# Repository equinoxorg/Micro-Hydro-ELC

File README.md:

hydrocontroller-hardware-designs
================================

This repository holds PCB/hardware designs for the e.quinox Kingfisher Micro Hydro Power Plant Controller.

Edit

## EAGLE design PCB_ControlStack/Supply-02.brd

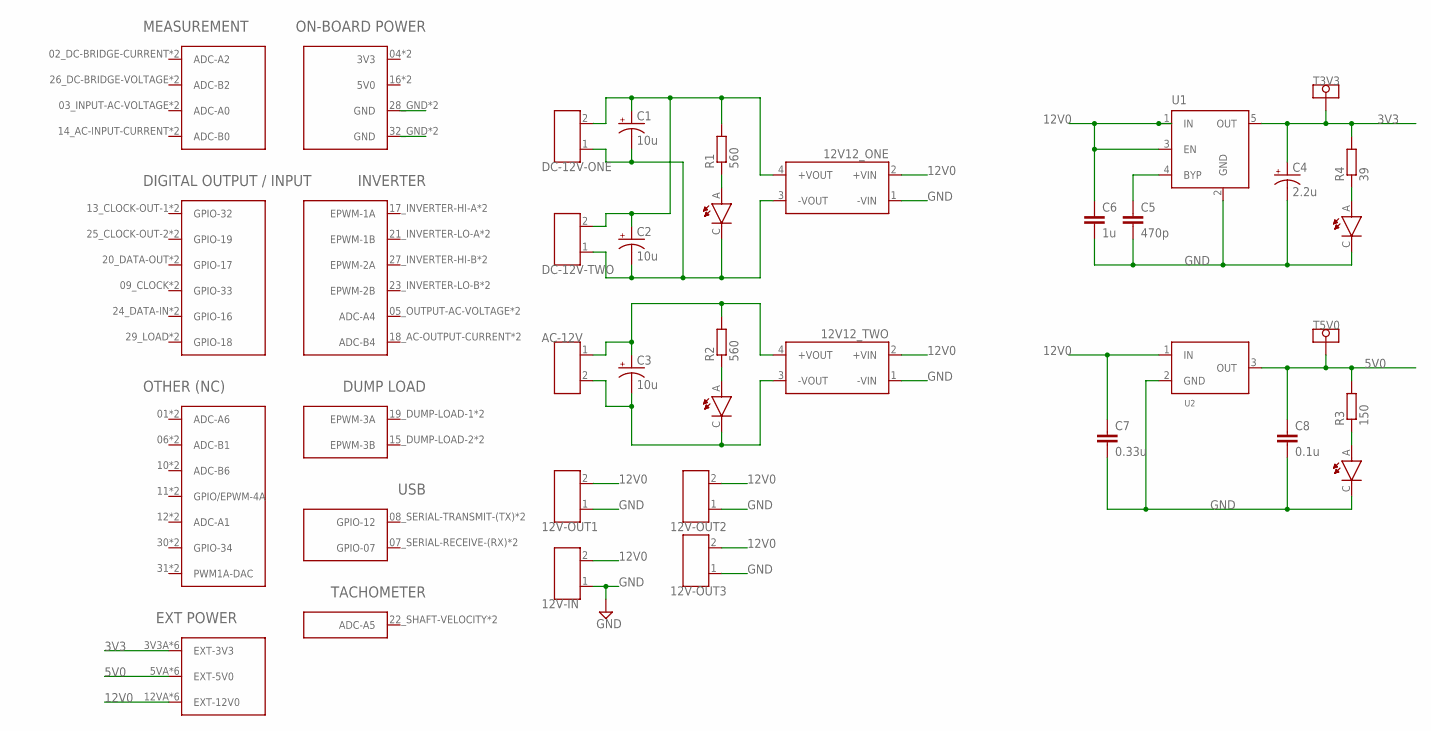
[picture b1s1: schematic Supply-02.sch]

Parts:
12V12_ONE, 12V12_TWO: 12V12_ISO_REG; SIL_REG
12V-IN, 12V-OUT1, 12V-OUT2, 12V-OUT3: 1X2_7,5_TB
AC-12V: 1X2_7,5_TB
C1, C2, C3: 10u; CPOL-4.0MM
C4: 2.2u; CPOL-4.0MM
C5: 470p; C0805
C6: 1u; C0805
C7: 0.33u; C0805
C8: 0.1u; C0805
DC-12V-ONE, DC-12V-TWO: 1X2_7,5_TB
H1: CONTROLLER_STACK
LED1, LED2, LED3, LED4: PLCC2
R1, R2: 560; R0805
R3: 150; R0805
R4: 39; R0805
T3V3, T5V0: TESTPAD
U1: MIC5219XX; SOT23-5
U2: 10V5V-REG-H; TO-220H

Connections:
3V3: C4.+, H1.3V3A (EXT-3V3), H1.3V3B (EXT-3V3), H1.3V3C (EXT-3V3), H1.3V3D (EXT-3V3), H1.3V3E (EXT-3V3), H1.3V3F (EXT-3V3), R4.2, T3V3.TP, U1.5 (OUT)
5V0: C8.1, H1.5VA (EXT-5V0), H1.5VB (EXT-5V0), H1.5VC (EXT-5V0), H1.5VD (EXT-5V0), H1.5VE (EXT-5V0), H1.5VF (EXT-5V0), R3.2, T5V0.TP, U2.3 (OUT)
12V0: 12V12_ONE.2 (+VIN), 12V12_TWO.2 (+VIN), 12V-IN.2, 12V-OUT1.2, 12V-OUT2.2, 12V-OUT3.2, C6.1, C7.1, H1.12VA (EXT-12V0), H1.12VB (EXT-12V0), H1.12VC (EXT-12V0), H1.12VD (EXT-12V0), H1.12VE (EXT-12V0), H1.12VF (EXT-12V0), U1.1 (IN), U1.3 (EN), U2.1 (IN)
GND: 12V12_ONE.1 (-VIN), 12V12_TWO.1 (-VIN), 12V-IN.1, 12V-OUT1.1, 12V-OUT2.1, 12V-OUT3.1, C4.-, C5.2, C6.2, C7.2, C8.2, H1.28_GND (GND), H1.32_GND (GND), H1.C28 (GND), H1.C32 (GND), LED3.C, LED4.C, U1.2 (GND), U2.2 (GND)
unnamed: 12V12_ONE.4 (+VOUT), C1.+, C2.+, DC-12V-ONE.2, DC-12V-TWO.2, R1.2
unnamed: 12V12_ONE.3 (-VOUT), C1.-, C2.-, DC-12V-ONE.1, DC-12V-TWO.1, LED1.C
unnamed: LED1.A, R1.1
unnamed: LED3.A, R3.1
unnamed: 12V12_TWO.3 (-VOUT), AC-12V.2, C3.-, LED2.C
unnamed: C5.1, U1.4 (BYP)
unnamed: LED2.A, R2.1
unnamed: 12V12_TWO.4 (+VOUT), AC-12V.1, C3.+, R2.2
unnamed: LED4.A, R4.1

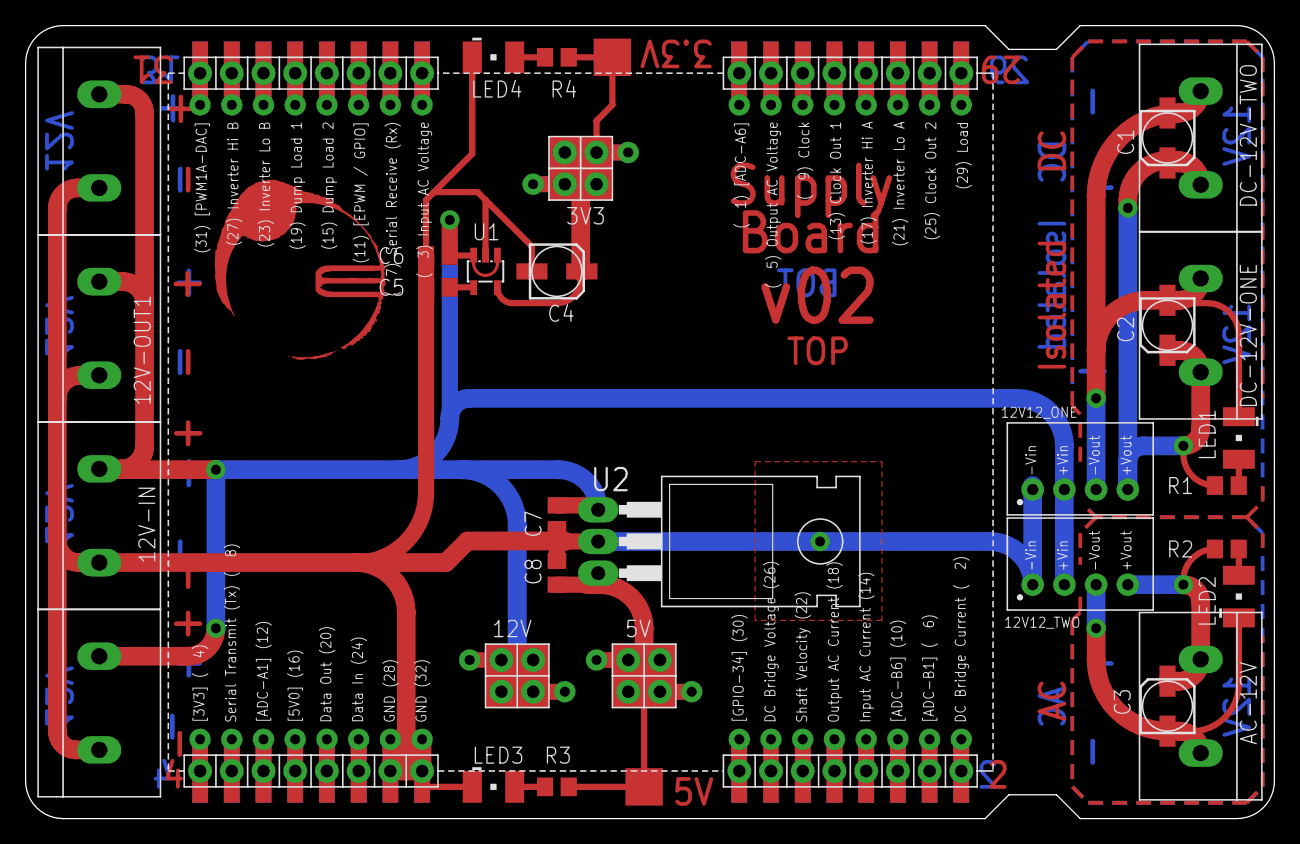
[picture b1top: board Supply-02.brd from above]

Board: 2 copper layers, 100.0 x 63.5 mm, 30 parts (0 on the bottom side), 13 nets.

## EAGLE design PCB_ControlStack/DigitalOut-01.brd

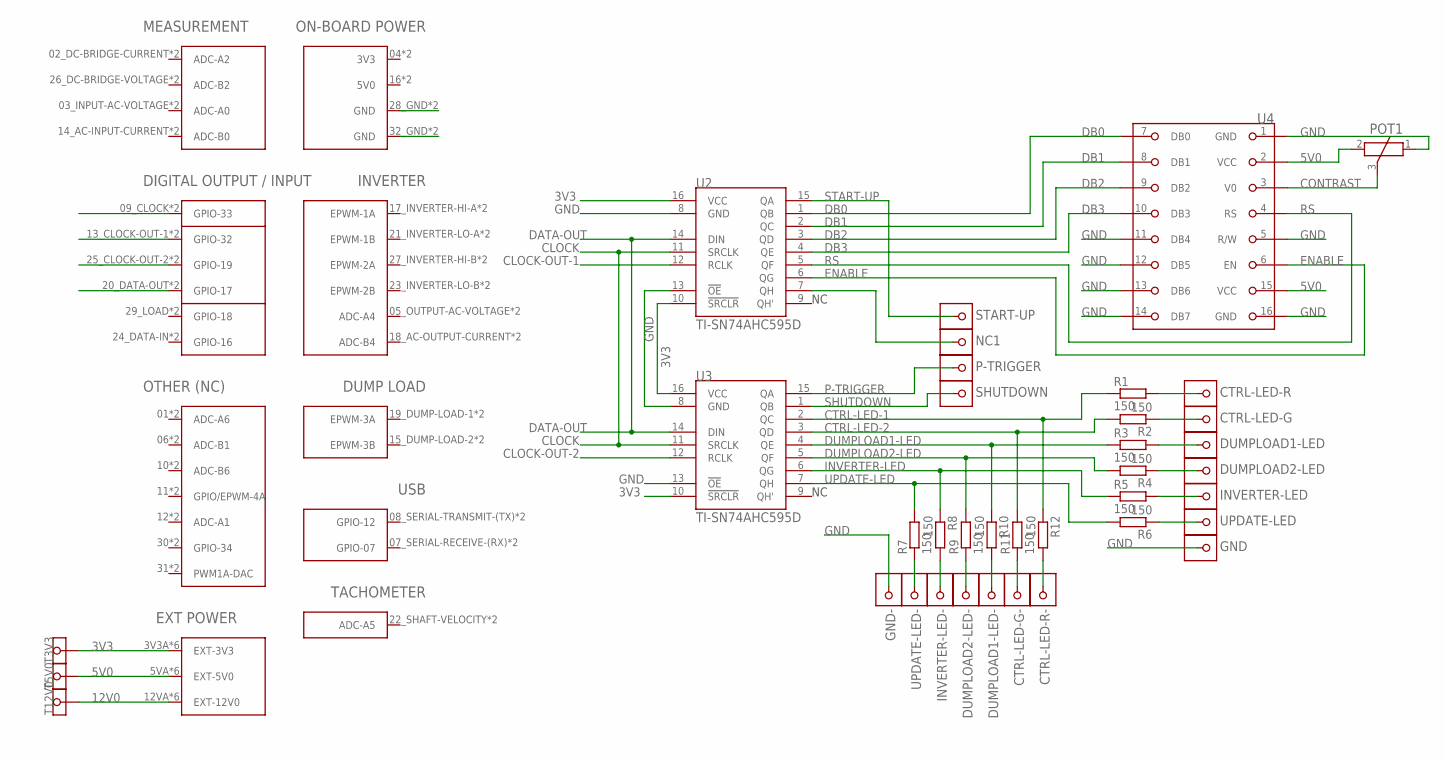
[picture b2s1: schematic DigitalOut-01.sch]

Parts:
CTRL-LED-G: 1X1HEADER(W/VIA)
CTRL-LED-G-: 1X1HEADER
CTRL-LED-R: 1X1HEADER(W/VIA)
CTRL-LED-R-: 1X1HEADER
DUMPLOAD1-LED, DUMPLOAD2-LED: 1X1HEADER(W/VIA)
DUMPLOAD1-LED-, DUMPLOAD2-LED-: 1X1HEADER
GND: 1X1HEADER(W/VIA)
GND-: 1X1HEADER
INVERTER-LED: 1X1HEADER(W/VIA)
INVERTER-LED-: 1X1HEADER
NC1: 1X1HEADER(W/VIA)
P-TRIGGER: 1X1HEADER(W/VIA)
POT1: BOURNS-3361S
R1, R2, R3, R4, R5, R6, R7, R8, R9, R10, R11, R12: 150; R0805
SHUTDOWN: 1X1HEADER(W/VIA)
START-UP: 1X1HEADER(W/VIA)
T3V3, T5V0, T12V0: TESTPAD
U1: CONTROLLER_STACK
U2, U3: TI-SN74AHC595D; SOIC-16D
U4: MULTICOMP-MC9B232
UPDATE-LED: 1X1HEADER(W/VIA)
UPDATE-LED-: 1X1HEADER

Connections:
3V3: T3V3.TP, U1.3V3A (EXT-3V3), U1.3V3B (EXT-3V3), U1.3V3C (EXT-3V3), U1.3V3D (EXT-3V3), U1.3V3E (EXT-3V3), U1.3V3F (EXT-3V3), U2.10 (!SRCLR), U2.16 (VCC), U3.10 (!SRCLR), U3.16 (VCC)
5V0: POT1.2, T5V0.TP, U1.5VA (EXT-5V0), U1.5VB (EXT-5V0), U1.5VC (EXT-5V0), U1.5VD (EXT-5V0), U1.5VE (EXT-5V0), U1.5VF (EXT-5V0), U4.2 (VCC), U4.15 (VCC)
12V0: T12V0.TP, U1.12VA (EXT-12V0), U1.12VB (EXT-12V0), U1.12VC (EXT-12V0), U1.12VD (EXT-12V0), U1.12VE (EXT-12V0), U1.12VF (EXT-12V0)
CLOCK: U1.09_CLOCK (GPIO-33), U1.C9 (GPIO-33), U2.11 (SRCLK), U3.11 (SRCLK)
CLOCK-OUT-1: U1.13_CLOCK-OUT-1 (GPIO-32), U1.C13 (GPIO-32), U2.12 (RCLK)
CLOCK-OUT-2: U1.25_CLOCK-OUT-2 (GPIO-19), U1.C25 (GPIO-19), U3.12 (RCLK)
CONTRAST: POT1.3, U4.3 (V0)
CTRL-LED-1: R1.1, R12.1, U3.2 (QC)
CTRL-LED-2: R2.2, R11.2, U3.3 (QD)
DATA-OUT: U1.20_DATA-OUT (GPIO-17), U1.C20 (GPIO-17), U2.14 (DIN), U3.14 (DIN)
DB0: U2.1 (QB), U4.7 (DB0)
DB1: U2.2 (QC), U4.8 (DB1)
DB2: U2.3 (QD), U4.9 (DB2)
DB3: U2.4 (QE), U4.10 (DB3)
DUMPLOAD1-LED: R3.1, R10.1, U3.4 (QE)
DUMPLOAD2-LED: R4.2, R9.2, U3.5 (QF)
ENABLE: U2.6 (QG), U4.6 (EN)
GND: GND.P$2, GND.P$3, GND.P$4, GND.PAD, GND-.P$1, POT1.1, U1.28_GND (GND), U1.32_GND (GND), U1.C28 (GND), U1.C32 (GND), U2.8 (GND), U2.13 (!OE), U3.8 (GND), U3.13 (!OE), U4.1 (GND), U4.5 (R/W), U4.11 (DB4), U4.12 (DB5), U4.13 (DB6), U4.14 (DB7), U4.16 (GND)
INVERTER-LED: R5.1, R8.1, U3.6 (QG)
unnamed: R7.1, UPDATE-LED-.P$1
unnamed: INVERTER-LED-.P$1, R8.2
unnamed: DUMPLOAD2-LED-.P$1, R9.1
unnamed: DUMPLOAD1-LED-.P$1, R10.2
unnamed: CTRL-LED-G-.P$1, R11.1
unnamed: CTRL-LED-R.P$2, CTRL-LED-R.P$3, CTRL-LED-R.P$4, CTRL-LED-R.PAD, R1.2
unnamed: CTRL-LED-R-.P$1, R12.2
unnamed: CTRL-LED-G.P$2, CTRL-LED-G.P$3, CTRL-LED-G.P$4, CTRL-LED-G.PAD, R2.1
unnamed: DUMPLOAD1-LED.P$2, DUMPLOAD1-LED.P$3, DUMPLOAD1-LED.P$4, DUMPLOAD1-LED.PAD, R3.2
unnamed: DUMPLOAD2-LED.P$2, DUMPLOAD2-LED.P$3, DUMPLOAD2-LED.P$4, DUMPLOAD2-LED.PAD, R4.1
unnamed: NC1.P$2, NC1.P$3, NC1.P$4, NC1.PAD, U2.7 (QH)
unnamed: INVERTER-LED.P$2, INVERTER-LED.P$3, INVERTER-LED.P$4, INVERTER-LED.PAD, R5.2
unnamed: R6.1, UPDATE-LED.P$2, UPDATE-LED.P$3, UPDATE-LED.P$4, UPDATE-LED.PAD
P-TRIGGER: P-TRIGGER.P$2, P-TRIGGER.P$3, P-TRIGGER.P$4, P-TRIGGER.PAD, U3.15 (QA)
RS: U2.5 (QF), U4.4 (RS)
SHUTDOWN: SHUTDOWN.P$2, SHUTDOWN.P$3, SHUTDOWN.P$4, SHUTDOWN.PAD, U3.1 (QB)
START-UP: START-UP.P$2, START-UP.P$3, START-UP.P$4, START-UP.PAD, U2.15 (QA)
UPDATE-LED: R6.2, R7.2, U3.7 (QH)

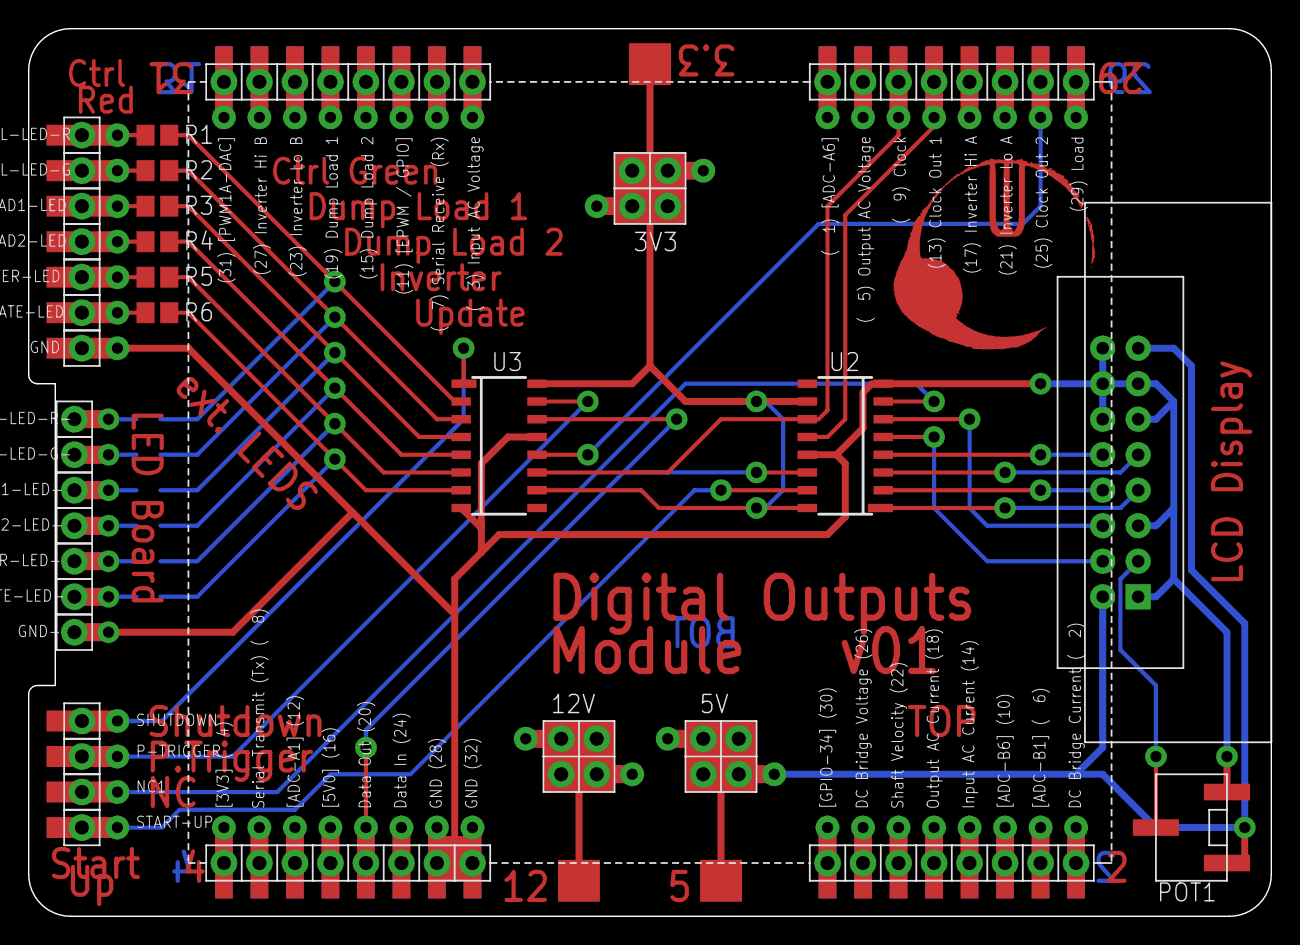
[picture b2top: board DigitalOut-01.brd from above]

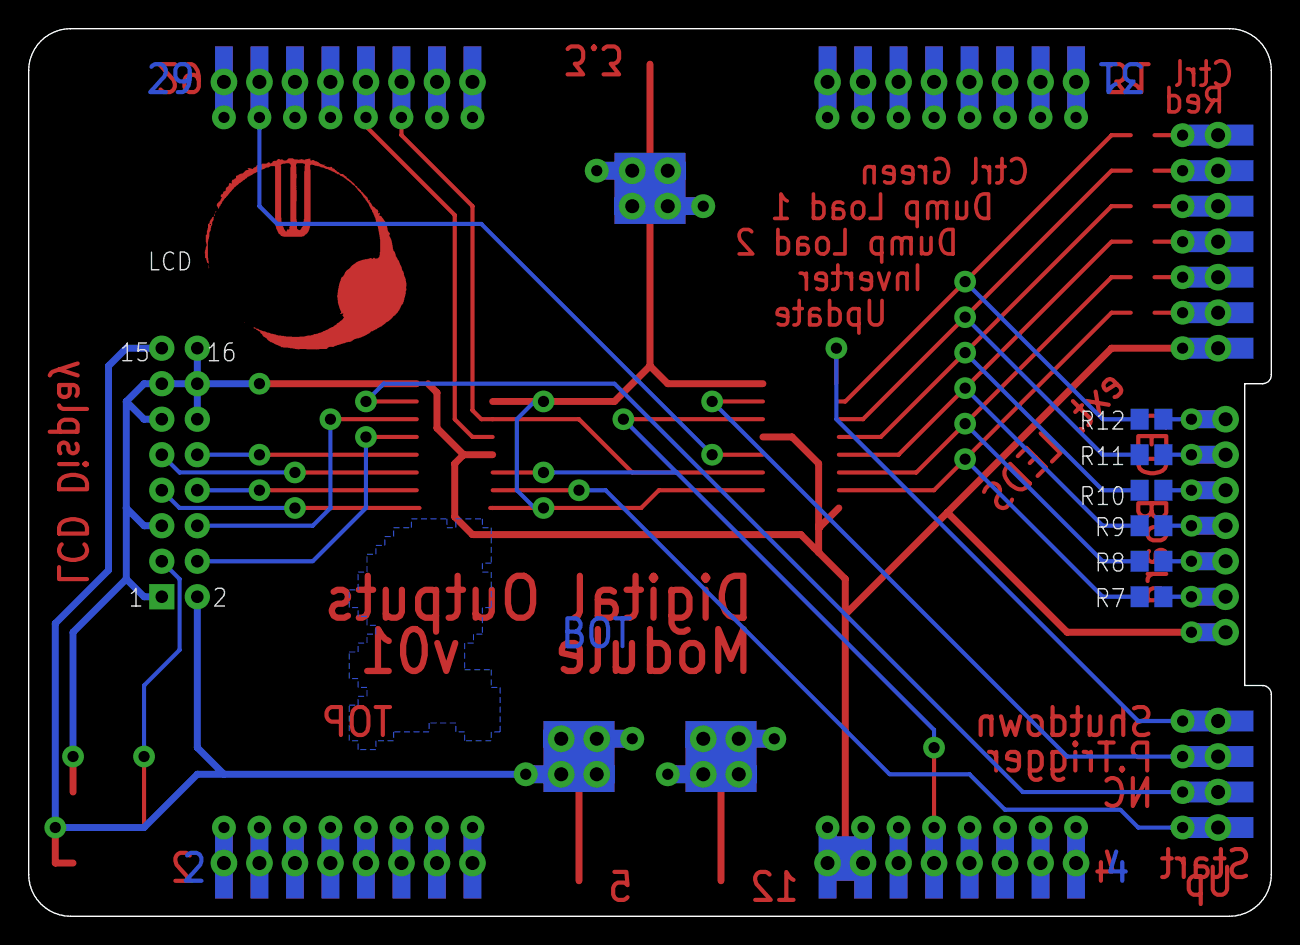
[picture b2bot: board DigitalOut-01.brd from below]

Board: 2 copper layers, 88.9 x 63.5 mm, 38 parts (6 on the bottom side), 37 nets.

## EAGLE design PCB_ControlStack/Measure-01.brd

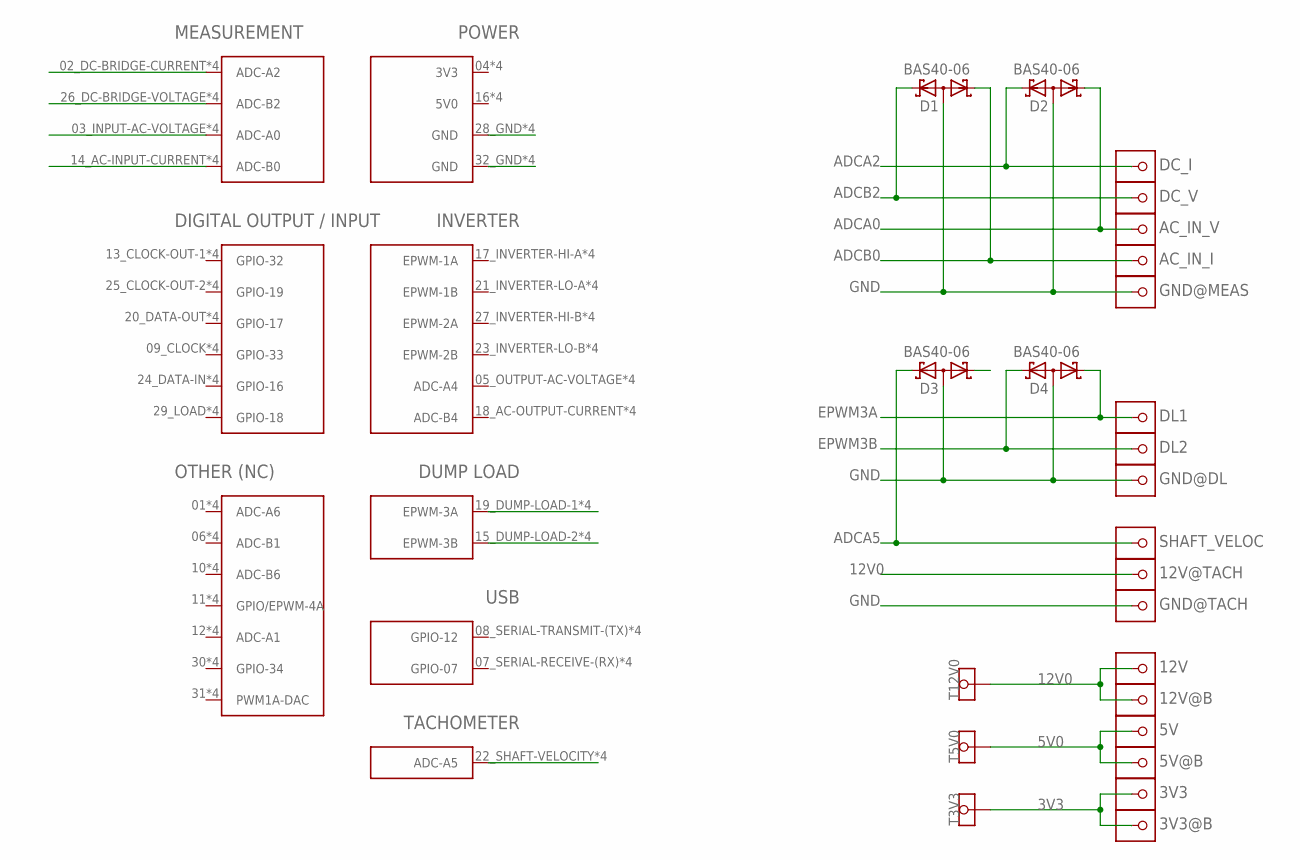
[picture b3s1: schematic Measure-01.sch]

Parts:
3V3, 3V3@B, 5V, 5V@B, 12V, 12V@B: 1X1STACK
12V@TACH: 1X1HEADER(W/VIA)
AC_IN_I: 1X1HEADER(W/VIA)
AC_IN_V: 1X1HEADER(W/VIA)
D1, D2, D3, D4: BAS40-06; SOT23
DC_I: 1X1HEADER(W/VIA)
DC_V: 1X1HEADER(W/VIA)
DL1, DL2: 1X1HEADER(W/VIA)
GND@DL: 1X1HEADER(W/VIA)
GND@MEAS: 1X1HEADER(W/VIA)
GND@TACH: 1X1HEADER(W/VIA)
SHAFT_VELOC: 1X1HEADER(W/VIA)
T3V3, T5V0, T12V0: TESTPAD
U$1: CONTROLLER_STACK

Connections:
3V3: 3V3.P$2, 3V3.P$5, 3V3.P$58, 3V3.P$65, 3V3.PAD, 3V3@B.P$2, 3V3@B.P$5, 3V3@B.P$58, 3V3@B.P$65, 3V3@B.PAD, T3V3.TP
5V0: 5V.P$2, 5V.P$5, 5V.P$58, 5V.P$65, 5V.PAD, 5V@B.P$2, 5V@B.P$5, 5V@B.P$58, 5V@B.P$65, 5V@B.PAD, T5V0.TP
12V0: 12V.P$2, 12V.P$5, 12V.P$58, 12V.P$65, 12V.PAD, 12V@B.P$2, 12V@B.P$5, 12V@B.P$58, 12V@B.P$65, 12V@B.PAD, 12V@TACH.P$2, 12V@TACH.P$3, 12V@TACH.P$4, 12V@TACH.PAD, T12V0.TP
ADCA0: AC_IN_V.P$2, AC_IN_V.P$3, AC_IN_V.P$4, AC_IN_V.PAD, D2.1 (K1), U$1.03_INPUT-AC-VOLTAGE (ADC-A0), U$1.A3 (ADC-A0), U$1.B3 (ADC-A0), U$1.C3 (ADC-A0)
ADCA2: D2.2 (K2), DC_I.P$2, DC_I.P$3, DC_I.P$4, DC_I.PAD, U$1.02_DC-BRIDGE-CURRENT (ADC-A2), U$1.A2 (ADC-A2), U$1.B2 (ADC-A2), U$1.C2 (ADC-A2)
ADCA5: D3.2 (K2), SHAFT_VELOC.P$2, SHAFT_VELOC.P$3, SHAFT_VELOC.P$4, SHAFT_VELOC.PAD, U$1.22_SHAFT-VELOCITY (ADC-A5), U$1.A22 (ADC-A5), U$1.B22 (ADC-A5), U$1.C22 (ADC-A5)
ADCB0: AC_IN_I.P$2, AC_IN_I.P$3, AC_IN_I.P$4, AC_IN_I.PAD, D1.1 (K1), U$1.14_AC-INPUT-CURRENT (ADC-B0), U$1.A14 (ADC-B0), U$1.B14 (ADC-B0), U$1.C14 (ADC-B0)
ADCB2: D1.2 (K2), DC_V.P$2, DC_V.P$3, DC_V.P$4, DC_V.PAD, U$1.26_DC-BRIDGE-VOLTAGE (ADC-B2), U$1.A26 (ADC-B2), U$1.B26 (ADC-B2), U$1.C26 (ADC-B2)
EPWM3A: D4.1 (K1), DL1.P$2, DL1.P$3, DL1.P$4, DL1.PAD, U$1.19_DUMP-LOAD-1 (EPWM-3A), U$1.A19 (EPWM-3A), U$1.B19 (EPWM-3A), U$1.C19 (EPWM-3A)
EPWM3B: D4.2 (K2), DL2.P$2, DL2.P$3, DL2.P$4, DL2.PAD, U$1.15_DUMP-LOAD-2 (EPWM-3B), U$1.A15 (EPWM-3B), U$1.B15 (EPWM-3B), U$1.C15 (EPWM-3B)
GND: D1.3 (AA), D2.3 (AA), D3.3 (AA), D4.3 (AA), GND@DL.P$2, GND@DL.P$3, GND@DL.P$4, GND@DL.PAD, GND@MEAS.P$2, GND@MEAS.P$3, GND@MEAS.P$4, GND@MEAS.PAD, GND@TACH.P$2, GND@TACH.P$3, GND@TACH.P$4, GND@TACH.PAD, U$1.28_GND (GND), U$1.32_GND (GND), U$1.A28 (GND), U$1.A32 (GND), U$1.B28 (GND), U$1.B32 (GND), U$1.C28 (GND), U$1.C32 (GND)
STARTUP: D3.1 (K1)

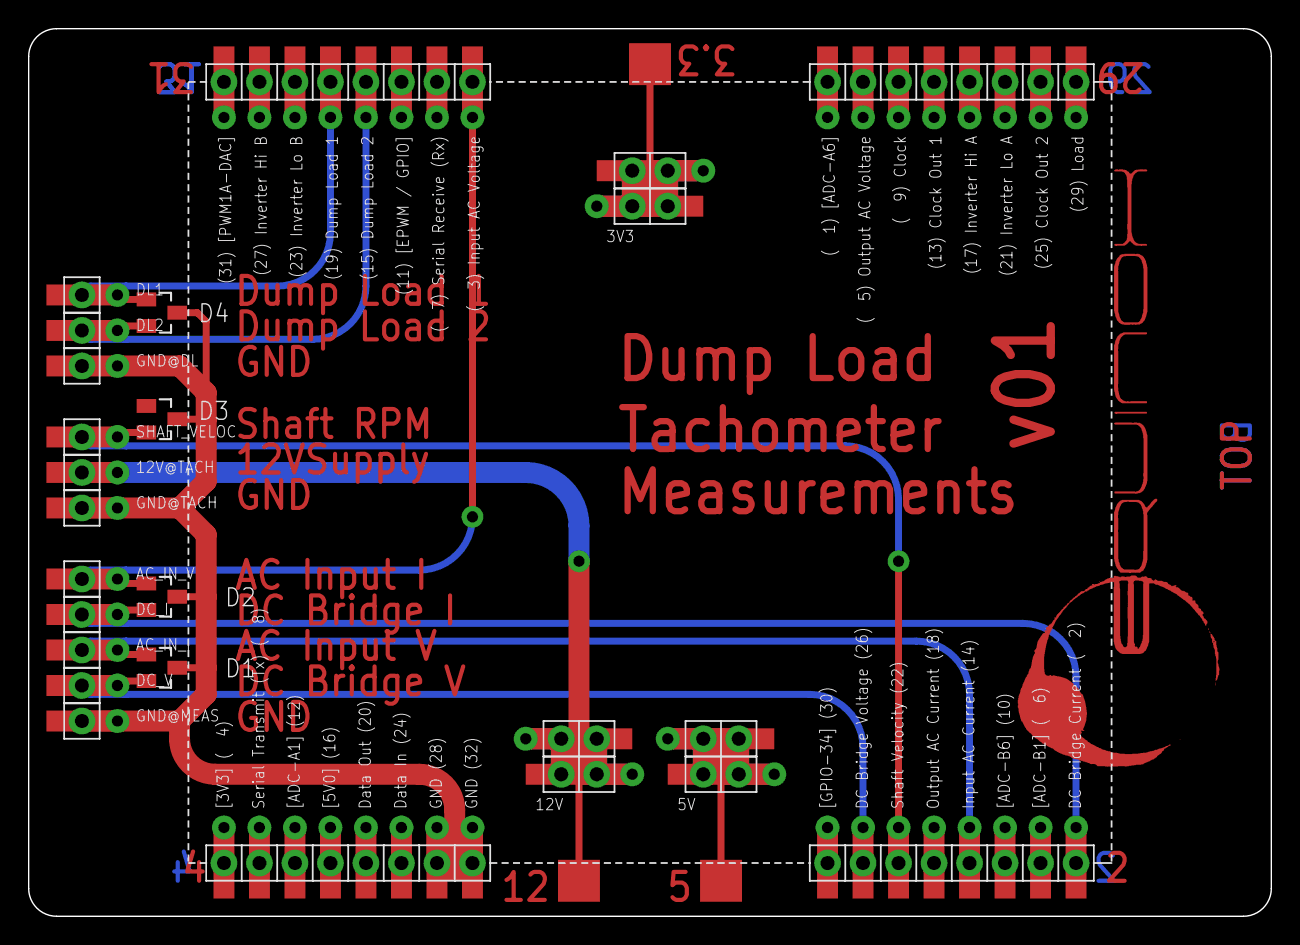
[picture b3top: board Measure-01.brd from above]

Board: 2 copper layers, 88.9 x 63.5 mm, 25 parts (0 on the bottom side), 11 nets.

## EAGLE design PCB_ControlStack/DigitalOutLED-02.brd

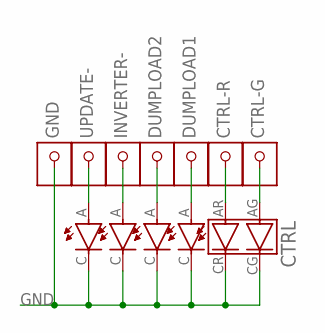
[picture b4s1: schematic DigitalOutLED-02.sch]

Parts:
CTRL: PLCC4-RG; PLCC4
CTRL-G: 1X1HEADER
CTRL-R: 1X1HEADER
DL1, DL2: PLCC2
DUMPLOAD1, DUMPLOAD2: 1X1HEADER
GND: 1X1HEADER
INVERTER: PLCC2
INVERTER-: 1X1HEADER
UPDATE: PLCC2
UPDATE-: 1X1HEADER

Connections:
GND: CTRL.CG, CTRL.CR, DL1.C, DL2.C, GND.P$1, INVERTER.C, UPDATE.C
unnamed: UPDATE.A, UPDATE-.P$1
unnamed: INVERTER.A, INVERTER-.P$1
unnamed: DL2.A, DUMPLOAD2.P$1
unnamed: DL1.A, DUMPLOAD1.P$1
unnamed: CTRL.AR, CTRL-R.P$1
unnamed: CTRL.AG, CTRL-G.P$1

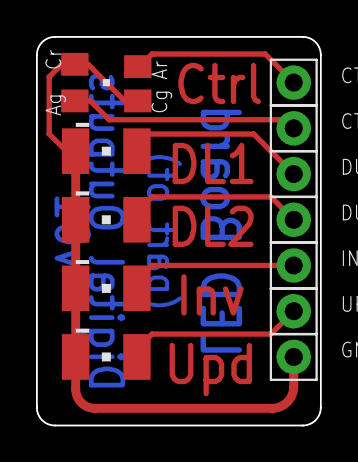
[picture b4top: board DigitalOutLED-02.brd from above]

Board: 2 copper layers, 15.8 x 21.6 mm, 12 parts (0 on the bottom side), 7 nets.

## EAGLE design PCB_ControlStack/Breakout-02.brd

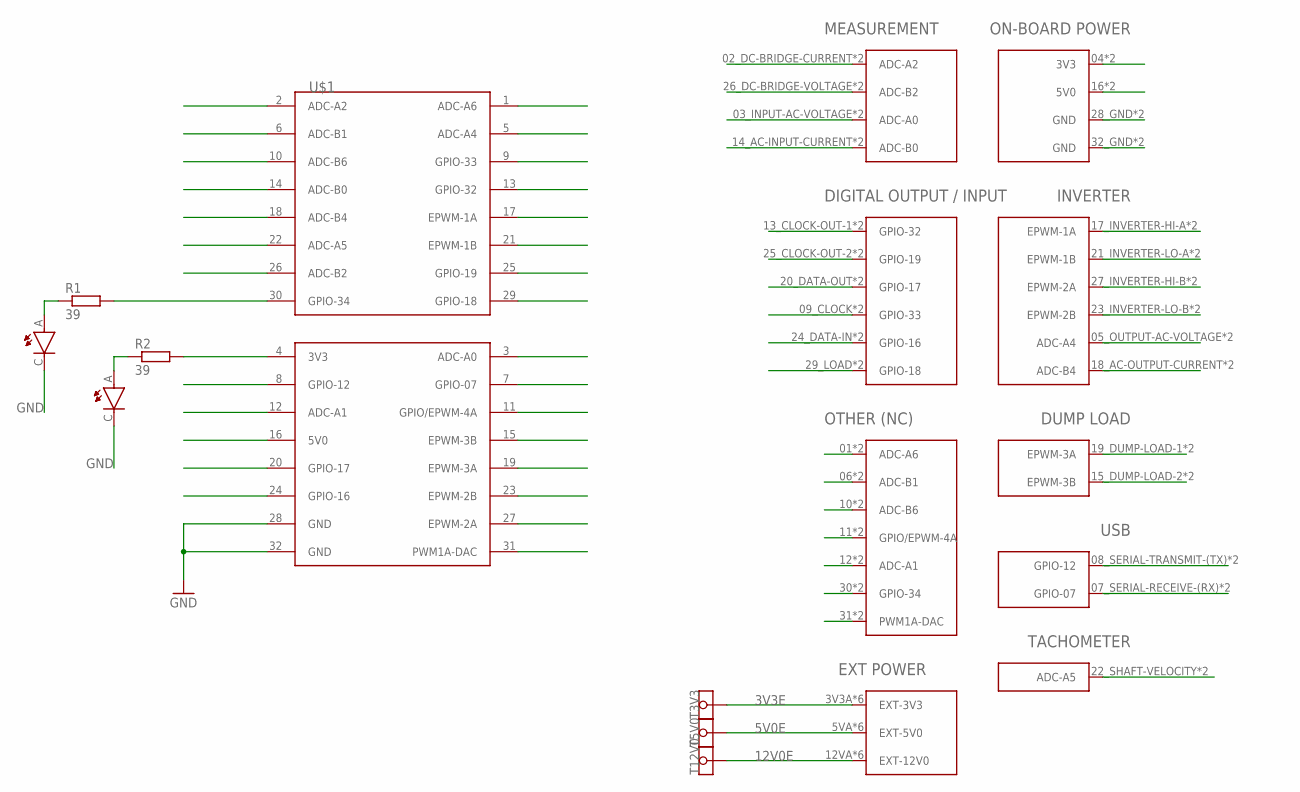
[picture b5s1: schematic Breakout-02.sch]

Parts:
GPIO34: PLCC2
PWR: PLCC2
R1, R2: 39; R0805
T3V3, T5V0, T12V0: TESTPAD
U$1: CONTROLLER_SOCKET
U$2: CONTROLLER_STACK

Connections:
3V3: R2.2, U$1.4 (3V3), U$2.04 (3V3), U$2.C4 (3V3)
3V3E: T3V3.TP, U$2.3V3A (EXT-3V3), U$2.3V3B (EXT-3V3), U$2.3V3C (EXT-3V3), U$2.3V3D (EXT-3V3), U$2.3V3E (EXT-3V3), U$2.3V3F (EXT-3V3)
5V0: U$1.16 (5V0), U$2.16 (5V0), U$2.C16 (5V0)
5V0E: T5V0.TP, U$2.5VA (EXT-5V0), U$2.5VB (EXT-5V0), U$2.5VC (EXT-5V0), U$2.5VD (EXT-5V0), U$2.5VE (EXT-5V0), U$2.5VF (EXT-5V0)
12V0E: T12V0.TP, U$2.12VA (EXT-12V0), U$2.12VB (EXT-12V0), U$2.12VC (EXT-12V0), U$2.12VD (EXT-12V0), U$2.12VE (EXT-12V0), U$2.12VF (EXT-12V0)
ADCA0: U$1.3 (ADC-A0), U$2.03_INPUT-AC-VOLTAGE (ADC-A0), U$2.C3 (ADC-A0)
ADCA1: U$1.12 (ADC-A1), U$2.12 (ADC-A1), U$2.C12 (ADC-A1)
ADCA2: U$1.2 (ADC-A2), U$2.02_DC-BRIDGE-CURRENT (ADC-A2), U$2.C2 (ADC-A2)
ADCA4: U$1.5 (ADC-A4), U$2.05_OUTPUT-AC-VOLTAGE (ADC-A4), U$2.C5 (ADC-A4)
ADCA5: U$1.22 (ADC-A5), U$2.22_SHAFT-VELOCITY (ADC-A5), U$2.C22 (ADC-A5)
ADCA6: U$1.1 (ADC-A6), U$2.01 (ADC-A6), U$2.C1 (ADC-A6)
ADCB0: U$1.14 (ADC-B0), U$2.14_AC-INPUT-CURRENT (ADC-B0), U$2.C14 (ADC-B0)
ADCB1: U$1.6 (ADC-B1), U$2.06 (ADC-B1), U$2.C6 (ADC-B1)
ADCB2: U$1.26 (ADC-B2), U$2.26_DC-BRIDGE-VOLTAGE (ADC-B2), U$2.C26 (ADC-B2)
ADCB4: U$1.18 (ADC-B4), U$2.18_AC-OUTPUT-CURRENT (ADC-B4), U$2.C18 (ADC-B4)
ADCB6: U$1.10 (ADC-B6), U$2.10 (ADC-B6), U$2.C10 (ADC-B6)
EPWM1A: U$1.17 (EPWM-1A), U$2.17_INVERTER-HI-A (EPWM-1A), U$2.C17 (EPWM-1A)
EPWM1B: U$1.21 (EPWM-1B), U$2.21_INVERTER-LO-A (EPWM-1B), U$2.C21 (EPWM-1B)
EPWM2A: U$1.27 (EPWM-2A), U$2.27_INVERTER-HI-B (EPWM-2A), U$2.C27 (EPWM-2A)
EPWM2B: U$1.23 (EPWM-2B), U$2.23_INVERTER-LO-B (EPWM-2B), U$2.C23 (EPWM-2B)
EPWM3A: U$1.19 (EPWM-3A), U$2.19_DUMP-LOAD-1 (EPWM-3A), U$2.C19 (EPWM-3A)
EPWM3B: U$1.15 (EPWM-3B), U$2.15_DUMP-LOAD-2 (EPWM-3B), U$2.C15 (EPWM-3B)
EPWM4A: U$1.11 (GPIO/EPWM-4A), U$2.11 (GPIO/EPWM-4A), U$2.C11 (GPIO/EPWM-4A)
GND: GPIO34.C, PWR.C, U$1.28 (GND), U$1.32 (GND), U$2.28_GND (GND), U$2.32_GND (GND), U$2.C28 (GND), U$2.C32 (GND)
GPIO07: U$1.7 (GPIO-07), U$2.07_SERIAL-RECEIVE-(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 (GPIO-07), U$2.C7 (GPIO-07)
GPIO12: U$1.8 (GPIO-12), U$2.08_SERIAL-TRANSMIT-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 (GPIO-12), U$2.C8 (GPIO-12)
GPIO16: U$1.24 (GPIO-16), U$2.24_DATA-IN (GPIO-16), U$2.C24 (GPIO-16)
GPIO17: U$1.20 (GPIO-17), U$2.20_DATA-OUT (GPIO-17), U$2.C20 (GPIO-17)
GPIO18: U$1.29 (GPIO-18), U$2.29_LOAD (GPIO-18), U$2.C29 (GPIO-18)
GPIO19: U$1.25 (GPIO-19), U$2.25_CLOCK-OUT-2 (GPIO-19), U$2.C25 (GPIO-19)
GPIO32: U$1.13 (GPIO-32), U$2.13_CLOCK-OUT-1 (GPIO-32), U$2.C13 (GPIO-32)
GPIO33: U$1.9 (GPIO-33), U$2.09_CLOCK (GPIO-33), U$2.C9 (GPIO-33)
GPIO34: R1.2, U$1.30 (GPIO-34), U$2.30 (GPIO-34), U$2.C30 (GPIO-34)
unnamed: PWR.A, R2.1
unnamed: GPIO34.A, R1.1
PWM1ADAC: U$1.31 (PWM1A-DAC), U$2.31 (PWM1A-DAC), U$2.C31 (PWM1A-DAC)

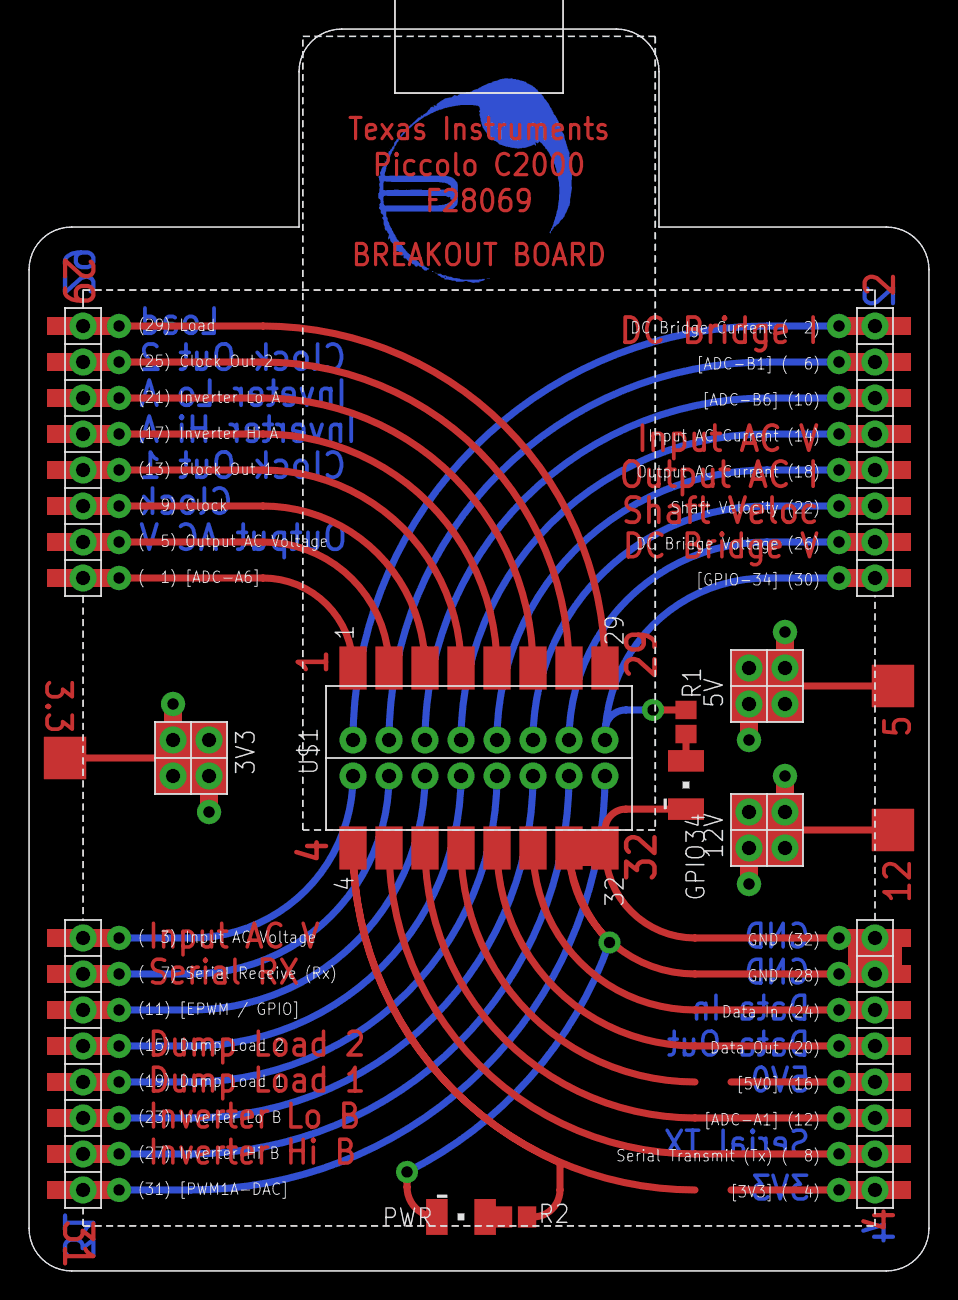
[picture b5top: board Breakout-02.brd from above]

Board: 2 copper layers, 63.5 x 87.6 mm, 9 parts (0 on the bottom side), 36 nets.

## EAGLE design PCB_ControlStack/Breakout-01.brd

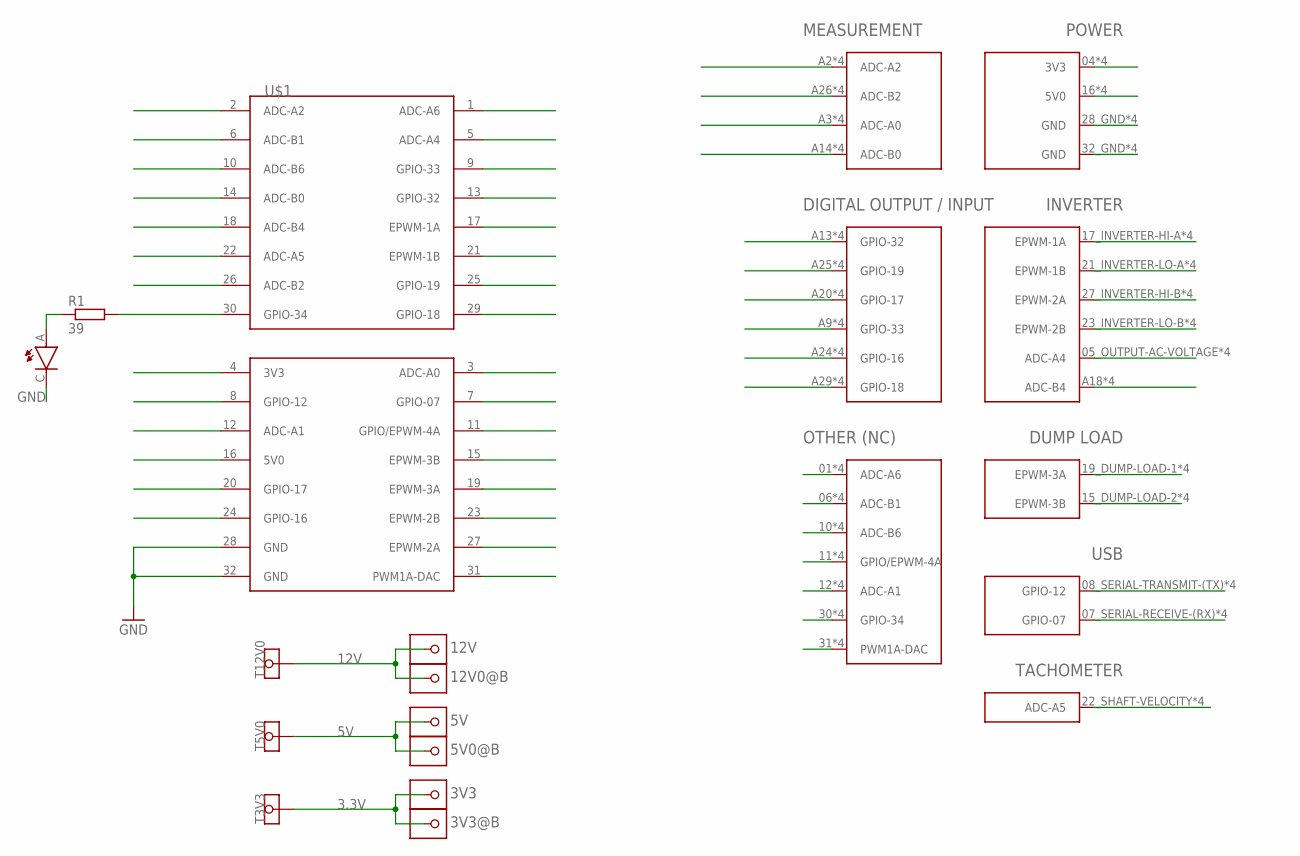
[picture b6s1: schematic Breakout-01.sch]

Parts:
3V3, 3V3@B, 5V, 5V0@B, 12V, 12V0@B: 1X1STACK
GPIO34: PLCC2
R1: 39; R0805
T3V3, T5V0, T12V0: TESTPAD
U$1: CONTROLLER_SOCKET
U$2: CONTROLLER_STACK

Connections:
3.3V: 3V3.P$2, 3V3.P$5, 3V3.P$58, 3V3.P$65, 3V3.PAD, 3V3@B.P$2, 3V3@B.P$5, 3V3@B.P$58, 3V3@B.P$65, 3V3@B.PAD, T3V3.TP
3V3: U$1.4 (3V3), U$2.04 (3V3), U$2.A4 (3V3), U$2.B4 (3V3), U$2.C4 (3V3)
5V: 5V.P$2, 5V.P$5, 5V.P$58, 5V.P$65, 5V.PAD, 5V0@B.P$2, 5V0@B.P$5, 5V0@B.P$58, 5V0@B.P$65, 5V0@B.PAD, T5V0.TP
5V0: U$1.16 (5V0), U$2.16 (5V0), U$2.A16 (5V0), U$2.B16 (5V0), U$2.C16 (5V0)
12V: 12V.P$2, 12V.P$5, 12V.P$58, 12V.P$65, 12V.PAD, 12V0@B.P$2, 12V0@B.P$5, 12V0@B.P$58, 12V0@B.P$65, 12V0@B.PAD, T12V0.TP
ADCA0: U$1.3 (ADC-A0), U$2.A3 (ADC-A0), U$2.B3 (ADC-A0), U$2.C3 (ADC-A0), U$2.INPUT-AC-VOLTAGE_03 (ADC-A0)
ADCA1: U$1.12 (ADC-A1), U$2.12 (ADC-A1), U$2.A12 (ADC-A1), U$2.B12 (ADC-A1), U$2.C12 (ADC-A1)
ADCA2: U$1.2 (ADC-A2), U$2.A2 (ADC-A2), U$2.B2 (ADC-A2), U$2.C2 (ADC-A2), U$2.DC-BRIDGE-CURRENT_02 (ADC-A2)
ADCA4: U$1.5 (ADC-A4), U$2.05_OUTPUT-AC-VOLTAGE (ADC-A4), U$2.A5 (ADC-A4), U$2.B5 (ADC-A4), U$2.C5 (ADC-A4)
ADCA5: U$1.22 (ADC-A5), U$2.22_SHAFT-VELOCITY (ADC-A5), U$2.A22 (ADC-A5), U$2.B22 (ADC-A5), U$2.C22 (ADC-A5)
ADCA6: U$1.1 (ADC-A6), U$2.01 (ADC-A6), U$2.A1 (ADC-A6), U$2.B1 (ADC-A6), U$2.C1 (ADC-A6)
ADCB0: U$1.14 (ADC-B0), U$2.A14 (ADC-B0), U$2.AC-INPUT-CURRENT_14 (ADC-B0), U$2.B14 (ADC-B0), U$2.C14 (ADC-B0)
ADCB1: U$1.6 (ADC-B1), U$2.06 (ADC-B1), U$2.A6 (ADC-B1), U$2.B6 (ADC-B1), U$2.C6 (ADC-B1)
ADCB2: U$1.26 (ADC-B2), U$2.A26 (ADC-B2), U$2.B26 (ADC-B2), U$2.C26 (ADC-B2), U$2.DC-BRIDGE-VOLTAGE_26 (ADC-B2)
ADCB4: U$1.18 (ADC-B4), U$2.A18 (ADC-B4), U$2.AC-OUTPUT-CURRENT_18 (ADC-B4), U$2.B18 (ADC-B4), U$2.C18 (ADC-B4)
ADCB6: U$1.10 (ADC-B6), U$2.10 (ADC-B6), U$2.A10 (ADC-B6), U$2.B10 (ADC-B6), U$2.C10 (ADC-B6)
EPWM1A: U$1.17 (EPWM-1A), U$2.17_INVERTER-HI-A (EPWM-1A), U$2.A17 (EPWM-1A), U$2.B17 (EPWM-1A), U$2.C17 (EPWM-1A)
EPWM1B: U$1.21 (EPWM-1B), U$2.21_INVERTER-LO-A (EPWM-1B), U$2.A21 (EPWM-1B), U$2.B21 (EPWM-1B), U$2.C21 (EPWM-1B)
EPWM2A: U$1.27 (EPWM-2A), U$2.27_INVERTER-HI-B (EPWM-2A), U$2.A27 (EPWM-2A), U$2.B27 (EPWM-2A), U$2.C27 (EPWM-2A)
EPWM2B: U$1.23 (EPWM-2B), U$2.23_INVERTER-LO-B (EPWM-2B), U$2.A23 (EPWM-2B), U$2.B23 (EPWM-2B), U$2.C23 (EPWM-2B)
EPWM3A: U$1.19 (EPWM-3A), U$2.19_DUMP-LOAD-1 (EPWM-3A), U$2.A19 (EPWM-3A), U$2.B19 (EPWM-3A), U$2.C19 (EPWM-3A)
EPWM3B: U$1.15 (EPWM-3B), U$2.15_DUMP-LOAD-2 (EPWM-3B), U$2.A15 (EPWM-3B), U$2.B15 (EPWM-3B), U$2.C15 (EPWM-3B)
EPWM4A: U$1.11 (GPIO/EPWM-4A), U$2.11 (GPIO/EPWM-4A), U$2.A11 (GPIO/EPWM-4A), U$2.B11 (GPIO/EPWM-4A), U$2.C11 (GPIO/EPWM-4A)
GND: GPIO34.C, U$1.28 (GND), U$1.32 (GND), U$2.28_GND (GND), U$2.32_GND (GND), U$2.A28 (GND), U$2.A32 (GND), U$2.B28 (GND), U$2.B32 (GND), U$2.C28 (GND), U$2.C32 (GND)
GPIO07: U$1.7 (GPIO-07), U$2.07_SERIAL-RECEIVE-(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 (GPIO-07), U$2.A7 (GPIO-07), U$2.B7 (GPIO-07), U$2.C7 (GPIO-07)
GPIO12: U$1.8 (GPIO-12), U$2.08_SERIAL-TRANSMIT-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 (GPIO-12), U$2.A8 (GPIO-12), U$2.B8 (GPIO-12), U$2.C8 (GPIO-12)
GPIO16: U$1.24 (GPIO-16), U$2.A24 (GPIO-16), U$2.B24 (GPIO-16), U$2.C24 (GPIO-16), U$2.DATA-IN_24 (GPIO-16)
GPIO17: U$1.20 (GPIO-17), U$2.A20 (GPIO-17), U$2.B20 (GPIO-17), U$2.C20 (GPIO-17), U$2.DATA-OUT_20 (GPIO-17)
GPIO18: U$1.29 (GPIO-18), U$2.A29 (GPIO-18), U$2.B29 (GPIO-18), U$2.C29 (GPIO-18), U$2.LOAD_29 (GPIO-18)
GPIO19: U$1.25 (GPIO-19), U$2.A25 (GPIO-19), U$2.B25 (GPIO-19), U$2.C25 (GPIO-19), U$2.CLOCK-OUT-2_25 (GPIO-19)
GPIO32: U$1.13 (GPIO-32), U$2.A13 (GPIO-32), U$2.B13 (GPIO-32), U$2.C13 (GPIO-32), U$2.CLOCK-OUT-1_13 (GPIO-32)
GPIO33: U$1.9 (GPIO-33), U$2.A9 (GPIO-33), U$2.B9 (GPIO-33), U$2.C9 (GPIO-33), U$2.CLOCK_09 (GPIO-33)
GPIO34: R1.2, U$1.30 (GPIO-34), U$2.30 (GPIO-34), U$2.A30 (GPIO-34), U$2.B30 (GPIO-34), U$2.C30 (GPIO-34)
unnamed: GPIO34.A, R1.1
PWM1ADAC: U$1.31 (PWM1A-DAC), U$2.31 (PWM1A-DAC), U$2.A31 (PWM1A-DAC), U$2.B31 (PWM1A-DAC), U$2.C31 (PWM1A-DAC)

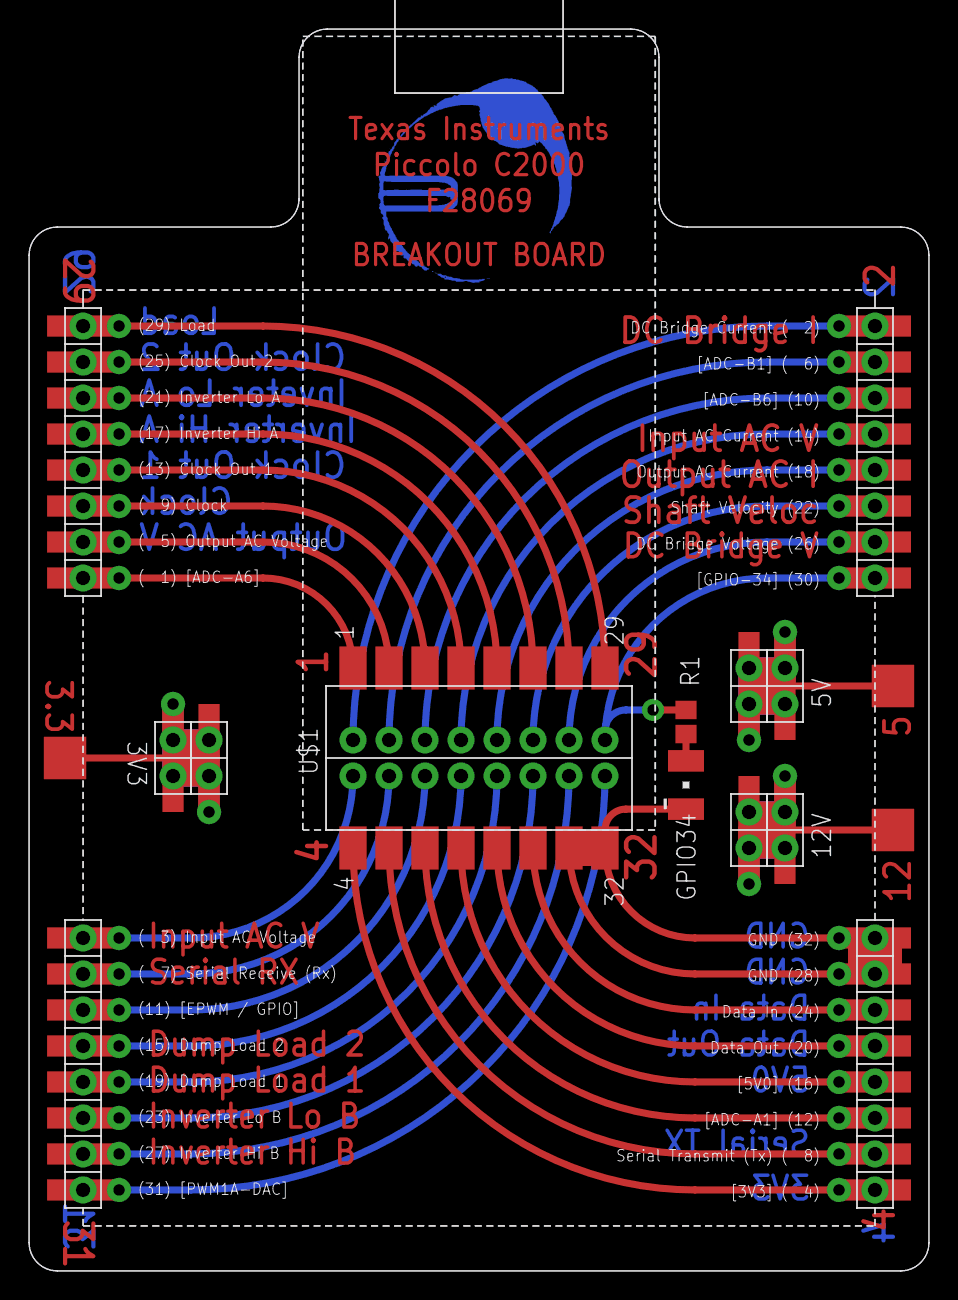
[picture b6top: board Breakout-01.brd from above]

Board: 2 copper layers, 63.5 x 87.6 mm, 13 parts (0 on the bottom side), 35 nets.
